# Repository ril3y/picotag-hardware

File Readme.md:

# PicoTag – Hardware Overview

**PicoTag** is a compact hardware reverse engineering and interface discovery board powered by the Raspberry Pi Pico W. It is designed for embedded developers and security researchers who need to scan, probe, and interact with unknown hardware interfaces like JTAG, SWD, SPI, and UART. The board routes 16 GPIOs for flexible digital analysis, integrates a flash dumper interface, and supports a built-in terminal experience via USB.

---

## 🧠 Core Features

- **Powered by Raspberry Pi Pico W (RP2040W)**
  - Dual-core ARM Cortex-M0+
  - USB-CDC console for interacting with the onboard terminal (SpicyTerm)
  - Wi-Fi ready for future remote applications

- **Runs PicoTag Terminal**
  - Interactive command-line terminal over USB serial
  - Extensible command modules (JTAG scan, Flash dump, GPIO monitor, etc.)

- **Supports Analog Inputs (3.3V only)**
  - Safely connect analog signals for measurement and analysis

---

## ⚙️ GPIO Scan Interface

- **16 dedicated GPIO channels** labeled `CH01` to `CH16`
  - Direct 3.3 V logic (no level shifting)
  - Clearly labeled edge connector for easy probing
  - CH01/02 double as I2C (SDA/SCL)
  - CH09/10 double as UART (TX/RX)
  - CH07/08 labeled for PWM

- **All GPIOs referenced to 3.3 V domain**
  - Designed for direct connection to 3.3 V targets
  - Ground and 3.3 V rails provided next to scan header for scope or logic analyzer use

---

## 🔌 Flash Dumper Interface

- **Dedicated SPI flash dump section**
  - Labeled `FLASH DUMPER` with headers for:
    - `CS`, `CLK`, `MISO`, `MOSI`, `WP`, `HOLD`
  - Designed for quick clip-to-dump workflows using SOIC-8 flash clips
  - Jumper-selectable voltage (3.3 V-only)
  - Status LED indicates active operations

---

## 🧠 Control & I/O

- **Two tactile buttons**: `BTN1` and `BTN2`
  - Used for scan triggers, reset functions, or user-defined inputs

- **RESET button** for the Pico W

- **Visuals and labeling**
  - High-quality silkscreen labels for every interface
  - Clean corner mounting holes and rounded PCB edges

---

## 🔋 Power Supply

- **USB-powered (5 V input via Pico W USB)**
- Onboard LDO provides 3.3 V (shared with all logic and headers)
- 3.3 V and GND pins broken out at multiple locations

---

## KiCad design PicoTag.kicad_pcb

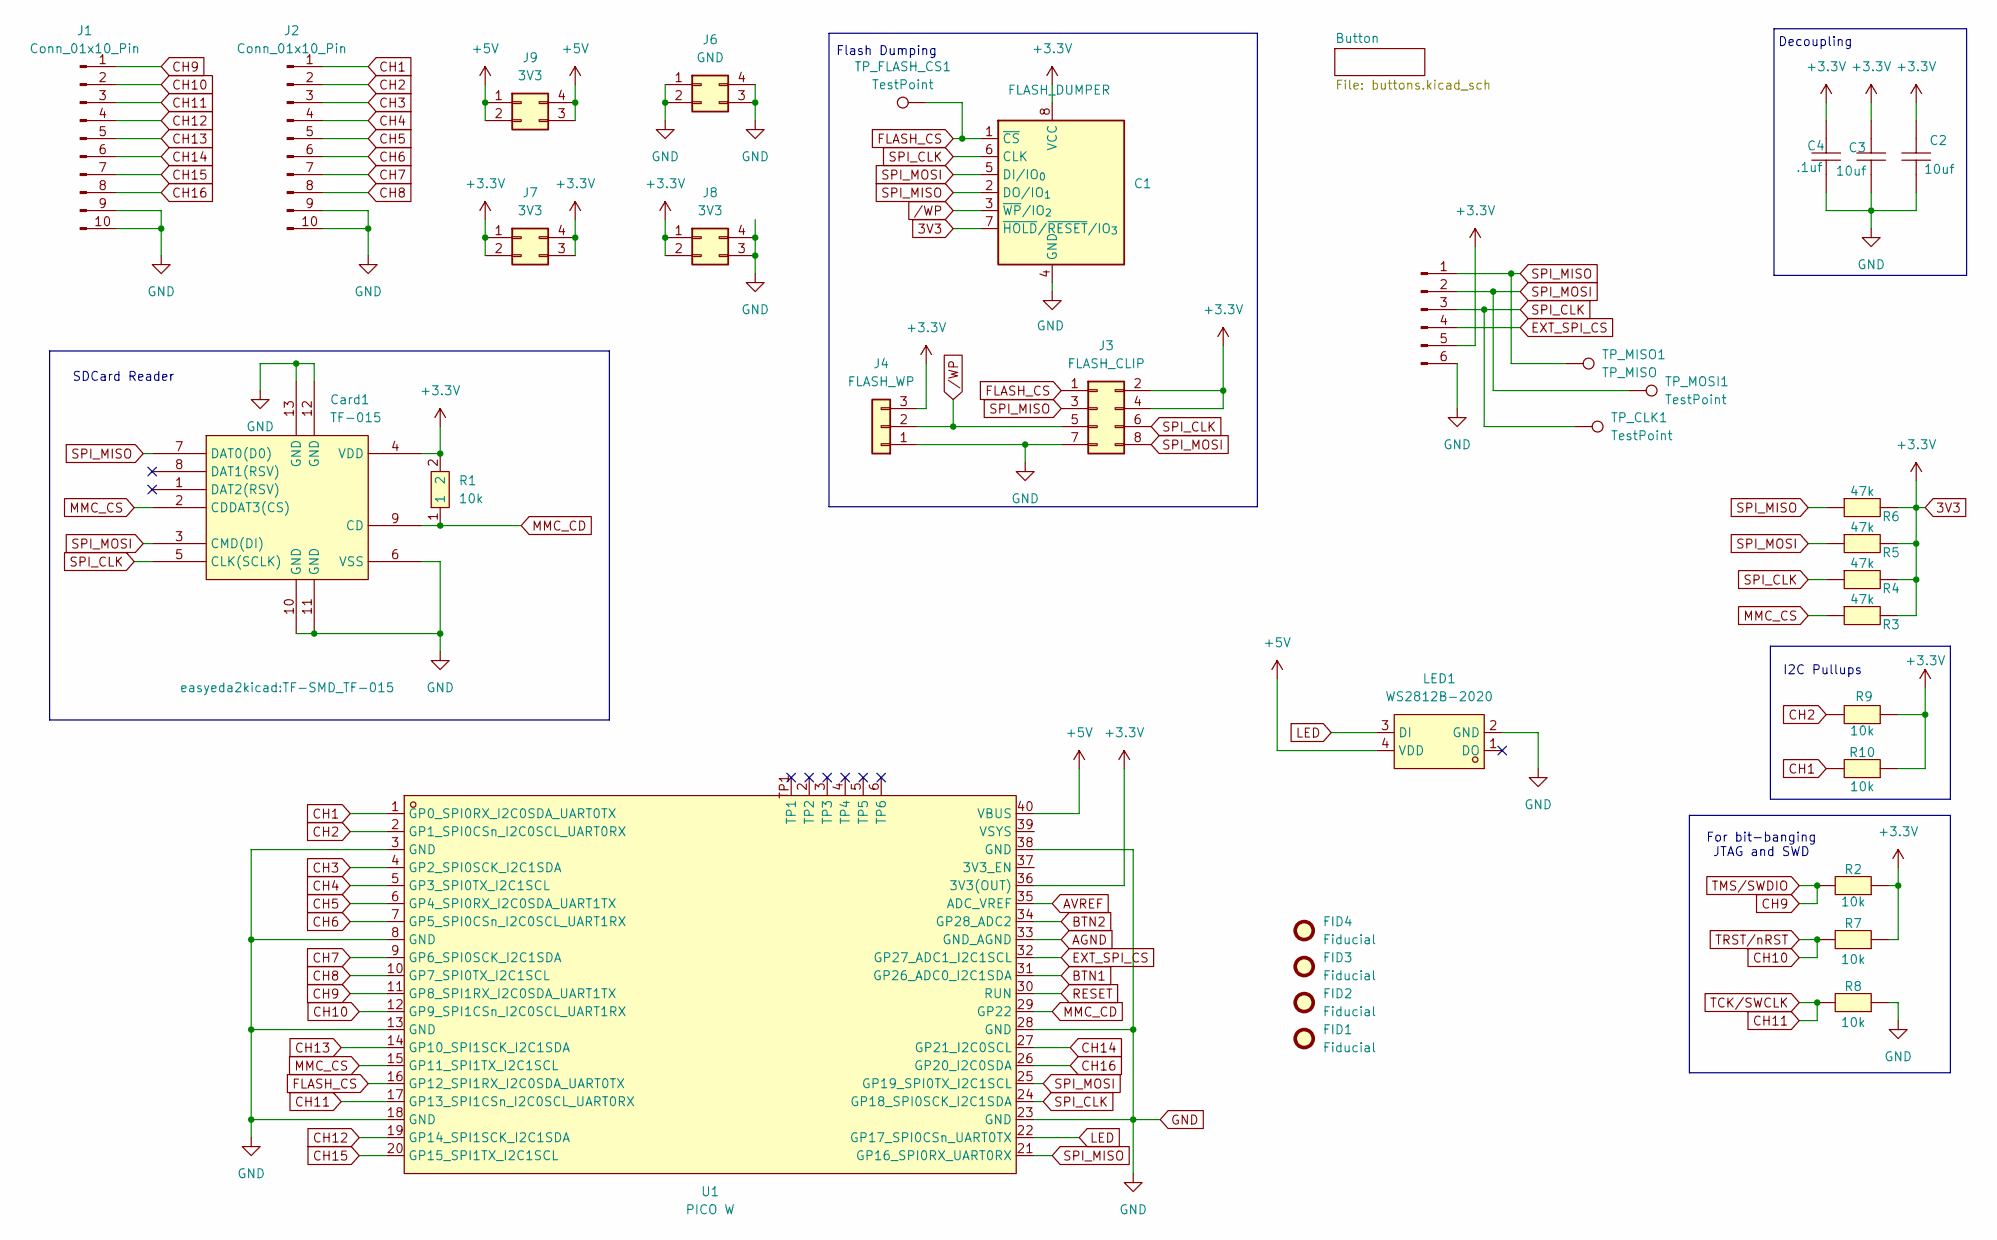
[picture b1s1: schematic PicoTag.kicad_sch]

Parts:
C1: FLASH_DUMPER; SOIC-8_5.3x5.3mm_P1.27mm flash dumper
C2, C3: 10uf; C_0603_1608Metric_Pad1.08x0.95mm_HandSolder; LCSC Part C1691
C4: .1uf; C_0603_1608Metric_Pad1.08x0.95mm_HandSolder; LCSC Part C1591
Card1: TF-015; TF-SMD_TF-015; LCSC Part C113206
FID1, FID2, FID3, FID4: Fiducial; Fiducial_0.5mm_Mask1mm
J1, J2: Conn_01x10_Pin; PinHeader_1x10_P2.54mm_Vertical
J3: FLASH_CLIP; PinHeader_2x04_P2.54mm_Vertical
J4: FLASH_WP; PinHeader_1x03_P2.54mm_Vertical
J6: GND; PinHeader_2x02_P2.54mm_Vertical
J7, J8, J9: 3V3; PinHeader_2x02_P2.54mm_Vertical
J11: Conn_01x06_Pin; PinHeader_1x06_P1.00mm_Vertical
LED1: WS2812B-2020; LED-SMD_4P-L2.0-W2.0-TL_WS2812B-2020; LCSC Part C965555
R1, R2, R7, R8, R9, R10: 10k; R_0603_1608Metric_Pad0.98x0.95mm_HandSolder; LCSC Part C2930027
R3, R4, R5, R6: 47k; R_0603_1608Metric_Pad0.98x0.95mm_HandSolder; LCSC Part C3016374
TP_CLK1: TestPoint; TestPoint_Pad_1.0x1.0mm
TP_FLASH_CS1: TestPoint; TestPoint_Pad_1.0x1.0mm
TP_MISO1: TP_MISO; TestPoint_Pad_1.0x1.0mm
TP_MOSI1: TestPoint; TestPoint_Pad_1.0x1.0mm
U1: PICO W; COMM-SMD_L51.0-W21.0-P2.54_PICOW; LCSC Part C7203003

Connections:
3V3: C1.7 (~HOLD/~RESET/IO_{3}), C1.8 (VCC), C2.2, C3.2, C4.2, Card1.4 (VDD), J3.2, J3.4, J4.3, J7.1, J7.2, J7.3, J7.4, J8.1, J8.2, J11.5, R1.2, R2.1, R3.2, R4.2, R5.2, R6.2, R7.1, R9.1, R10.1, U1.36 (3V3(OUT)); also elsewhere on the board
+5V: J9.1, J9.2, J9.3, J9.4, LED1.4 (VDD), U1.40 (VBUS)
AGND: U1.33 (GND_AGND)
AVREF: U1.35 (ADC_VREF)
BTN1: U1.31 (GP26_ADC0_I2C1SDA); also elsewhere on the board
BTN2: U1.34 (GP28_ADC2); also elsewhere on the board
CH1: J2.1, R10.2, U1.1 (GP0_SPI0RX_I2C0SDA_UART0TX)
CH2: J2.2, R9.2, U1.2 (GP1_SPI0CSn_I2C0SCL_UART0RX)
CH3: J2.3, U1.4 (GP2_SPI0SCK_I2C1SDA)
CH4: J2.4, U1.5 (GP3_SPI0TX_I2C1SCL)
CH5: J2.5, U1.6 (GP4_SPI0RX_I2C0SDA_UART1TX)
CH6: J2.6, U1.7 (GP5_SPI0CSn_I2C0SCL_UART1RX)
CH7: J2.7, U1.9 (GP6_SPI0SCK_I2C1SDA)
CH8: J2.8, U1.10 (GP7_SPI0TX_I2C1SCL)
CH9: J1.1, R2.2, U1.11 (GP8_SPI1RX_I2C0SDA_UART1TX)
CH10: J1.2, R7.2, U1.12 (GP9_SPI1CSn_I2C0SCL_UART1RX)
CH11: J1.3, R8.2, U1.17 (GP13_SPI1CSn_I2C0SCL_UART0RX)
CH12: J1.4, U1.19 (GP14_SPI1SCK_I2C1SDA)
CH13: J1.5, U1.14 (GP10_SPI1SCK_I2C1SDA)
CH14: J1.6, U1.27 (GP21_I2C0SCL)
CH15: J1.7, U1.20 (GP15_SPI1TX_I2C1SCL)
CH16: J1.8, U1.26 (GP20_I2C0SDA)
EXT_SPI_CS: J11.4, U1.32 (GP27_ADC1_I2C1SCL)
FLASH_CS: C1.1 (~CS), J3.1, TP_FLASH_CS1.1, U1.16 (GP12_SPI1RX_I2C0SDA_UART0TX)
GND: C1.4 (GND), C2.1, C3.1, C4.1, Card1.6 (VSS), Card1.10 (GND), Card1.11 (GND), Card1.12 (GND), Card1.13 (GND), J1.9, J1.10, J2.9, J2.10, J3.7, J4.1, J6.1, J6.2, J6.3, J6.4, J8.3, J8.4, J11.6, LED1.2 (GND), R8.1, U1.3 (GND), U1.8 (GND), U1.13 (GND), U1.18 (GND), U1.23 (GND), U1.28 (GND), U1.38 (GND); also elsewhere on the board
LED: LED1.3 (DI), U1.22 (GP17_SPI0CSn_UART0TX)
MMC_CD: Card1.9 (CD), R1.1, U1.29 (GP22)
MMC_CS: Card1.2 (CDDAT3(CS)), R3.1, U1.15 (GP11_SPI1TX_I2C1SCL)
RESET: U1.30 (RUN); also elsewhere on the board
SPI_CLK: C1.6 (CLK), Card1.5 (CLK(SCLK)), J3.6, J11.3, R4.1, TP_CLK1.1, U1.24 (GP18_SPI0SCK_I2C1SDA)
SPI_MISO: C1.2 (DO/IO_{1}), Card1.7 (DAT0(D0)), J3.3, J11.1, R6.1, TP_MISO1.1, U1.21 (GP16_SPI0RX_UART0RX)
SPI_MOSI: C1.5 (DI/IO_{0}), Card1.3 (CMD(DI)), J3.8, J11.2, R5.1, TP_MOSI1.1, U1.25 (GP19_SPI0TX_I2C1SCL)
/WP: C1.3 (~WP/IO_{2}), J3.5, J4.2

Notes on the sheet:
Flash Dumping
SDCard Reader
For bit-banging JTAG and SWD
Decoupling
I2C Pullups

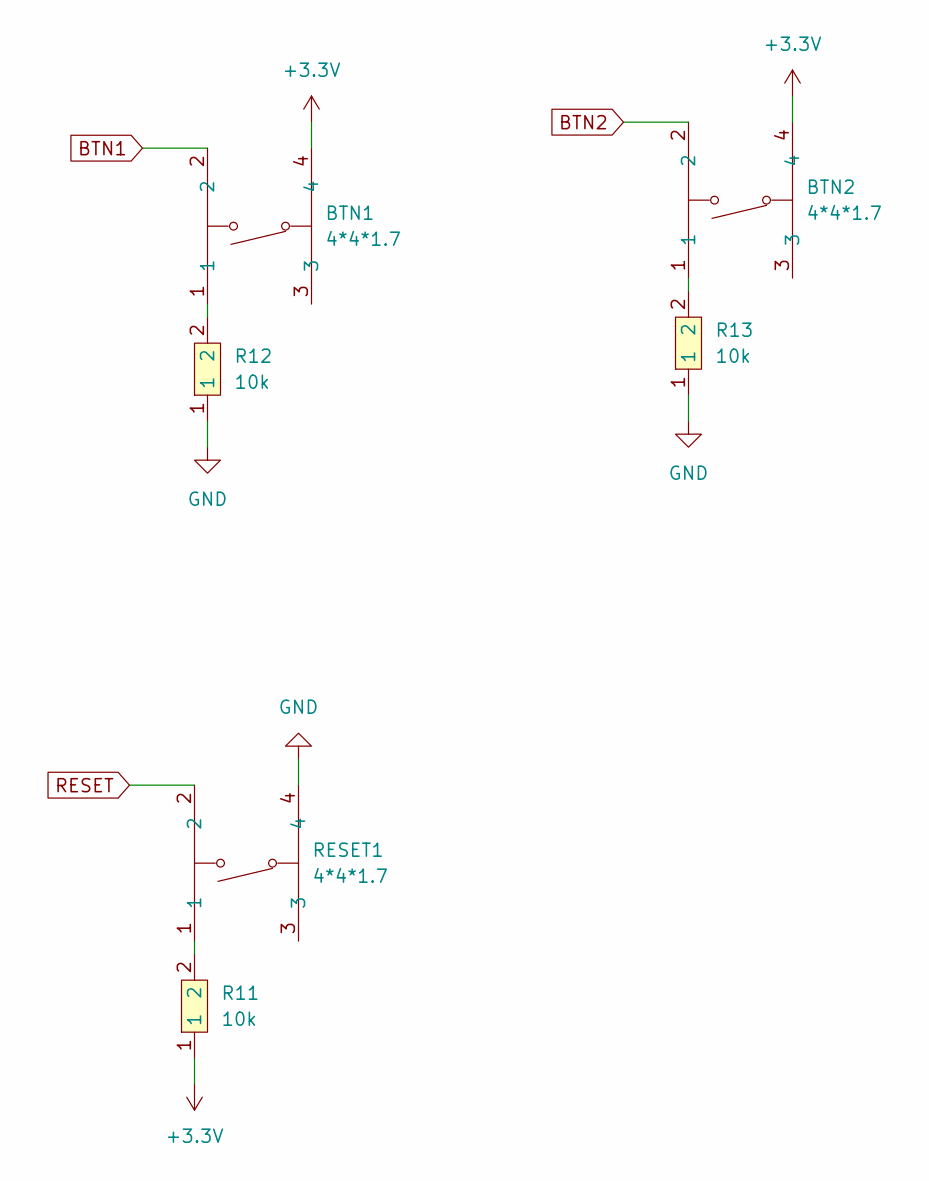
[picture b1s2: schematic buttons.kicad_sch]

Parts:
BTN1, BTN2: 4*4*1.7; SW-SMD_4P-L5.2-W5.2-P3.70-LS6.5; LCSC Part C10852
R11, R12, R13: 10k; R_0603_1608Metric_Pad0.98x0.95mm_HandSolder; LCSC Part C2930027
RESET1: 4*4*1.7; SW-SMD_4P-L5.2-W5.2-P3.70-LS6.5; LCSC Part C10852

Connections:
3V3: BTN1.4, BTN2.4, R11.1; also elsewhere on the board
BTN1: BTN1.2; also elsewhere on the board
BTN2: BTN2.2; also elsewhere on the board
GND: R12.1, R13.1, RESET1.4; also elsewhere on the board
unnamed: BTN1.1, R12.2
unnamed: BTN2.1, R13.2
unnamed: R11.2, RESET1.1
RESET: RESET1.2; also elsewhere on the board

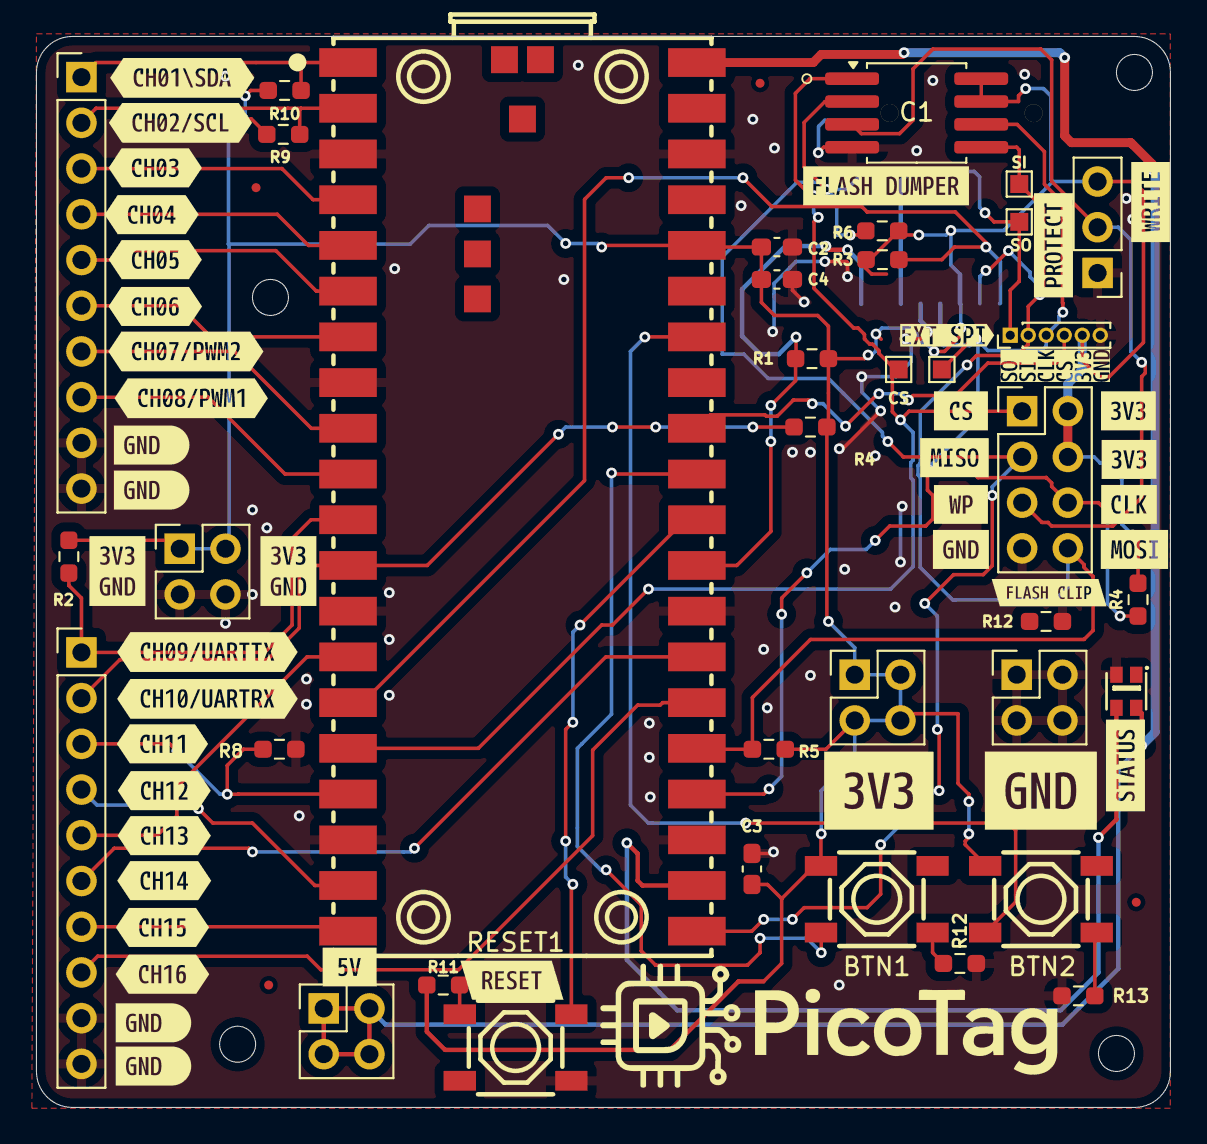
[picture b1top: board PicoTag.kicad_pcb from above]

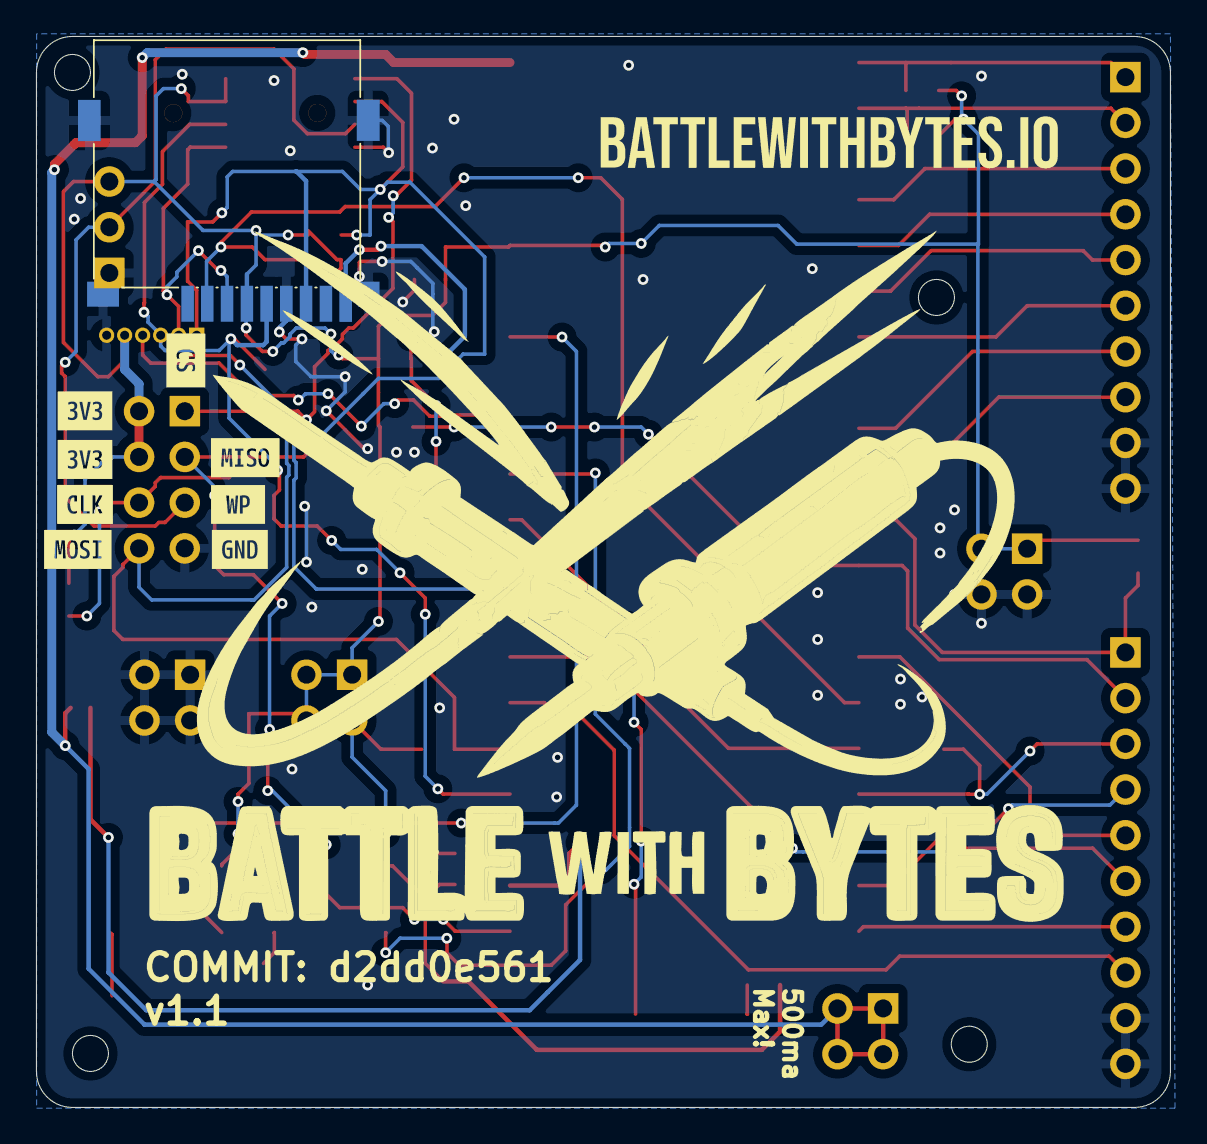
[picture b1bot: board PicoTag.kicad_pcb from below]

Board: 2 copper layers, 63.0 x 59.5 mm, 90 parts (9 on the bottom side), 34 nets.

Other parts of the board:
R12#2: 10k; R_0603_1608Metric_Pad0.98x0.95mm_HandSolder
kibuzzard-680A2A33: G***; kibuzzard-680A2A33
kibuzzard-680A2B2B: G***; kibuzzard-680A2B2B
kibuzzard-680A2B82: G***; kibuzzard-680A2B82
kibuzzard-680A26BF: G***; kibuzzard-680A26BF
kibuzzard-680A26E6: G***; kibuzzard-680A26E6
kibuzzard-680A26F2: G***; kibuzzard-680A26F2
kibuzzard-680A27E0, kibuzzard-680A27E0#2: G***; kibuzzard-680A27E0
kibuzzard-680A28B1: G***; kibuzzard-680A28B1
kibuzzard-680A28C8: G***; kibuzzard-680A28C8
kibuzzard-680A28D6: G***; kibuzzard-680A28D6
kibuzzard-680A28F0: G***; kibuzzard-680A28F0
kibuzzard-680A29B1: G***; kibuzzard-680A29B1
kibuzzard-680A29B9: G***; kibuzzard-680A29B9
kibuzzard-680A29C1: G***; kibuzzard-680A29C1
kibuzzard-680A29CB: G***; kibuzzard-680A29CB
kibuzzard-680A29D5: G***; kibuzzard-680A29D5
kibuzzard-680A29E5: G***; kibuzzard-680A29E5
kibuzzard-680A271C: G***; kibuzzard-680A271C
kibuzzard-680A273A: G***; kibuzzard-680A273A
kibuzzard-680A275A: G***; kibuzzard-680A275A
kibuzzard-680A280E: G***; kibuzzard-680A280E
kibuzzard-680A281D: G***; kibuzzard-680A281D
kibuzzard-680A282F, kibuzzard-680A282F#2: G***; kibuzzard-680A282F
kibuzzard-680A286D: G***; kibuzzard-680A286D
kibuzzard-680A291C: G***; kibuzzard-680A291C
kibuzzard-680A295C: G***; kibuzzard-680A295C
kibuzzard-680A296A: G***; kibuzzard-680A296A
kibuzzard-680A297B: G***; kibuzzard-680A297B
kibuzzard-680A2692: G***; kibuzzard-680A2692
kibuzzard-680A2725: G***; kibuzzard-680A2725
kibuzzard-680A2768, kibuzzard-680A2768#2, kibuzzard-680A2768#3: G***; kibuzzard-680A2768
kibuzzard-680A2774: G***; kibuzzard-680A2774
kibuzzard-680A2803: G***; kibuzzard-680A2803
kibuzzard-680A2843: G***; kibuzzard-680A2843
kibuzzard-680A2853: G***; kibuzzard-680A2853
kibuzzard-680A2862: G***; kibuzzard-680A2862
kibuzzard-680A2929: G***; kibuzzard-680A2929
kibuzzard-680A2935: G***; kibuzzard-680A2935
kibuzzard-680A2940: G***; kibuzzard-680A2940
kibuzzard-680A2949: G***; kibuzzard-680A2949
kibuzzard-680A2953: G***; kibuzzard-680A2953
kibuzzard-680A2987: G***; kibuzzard-680A2987
kibuzzard-68007E1C: G***; kibuzzard-68007E1C
kibuzzard-68007E04: G***; kibuzzard-68007E04
kibuzzard-68008EB3: G***; kibuzzard-68008EB3

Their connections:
GND: R12#2.1; also elsewhere on the board

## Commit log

2025-04-17 initial
2025-04-17 Add autosave and lock files to gitignore
2025-04-17 removeda file
2025-04-17 removed a file
2025-04-17 added hardware files
2025-04-17 hardware commit added
2025-04-17 added version
2025-04-24 Silkscreen fixes
2025-08-19 Update hardware design files and generate manufacturing outputs
    - Updated PCB layout and schematic files
    - Regenerated gerber files for manufacturing
    - Added BOM and plot files
